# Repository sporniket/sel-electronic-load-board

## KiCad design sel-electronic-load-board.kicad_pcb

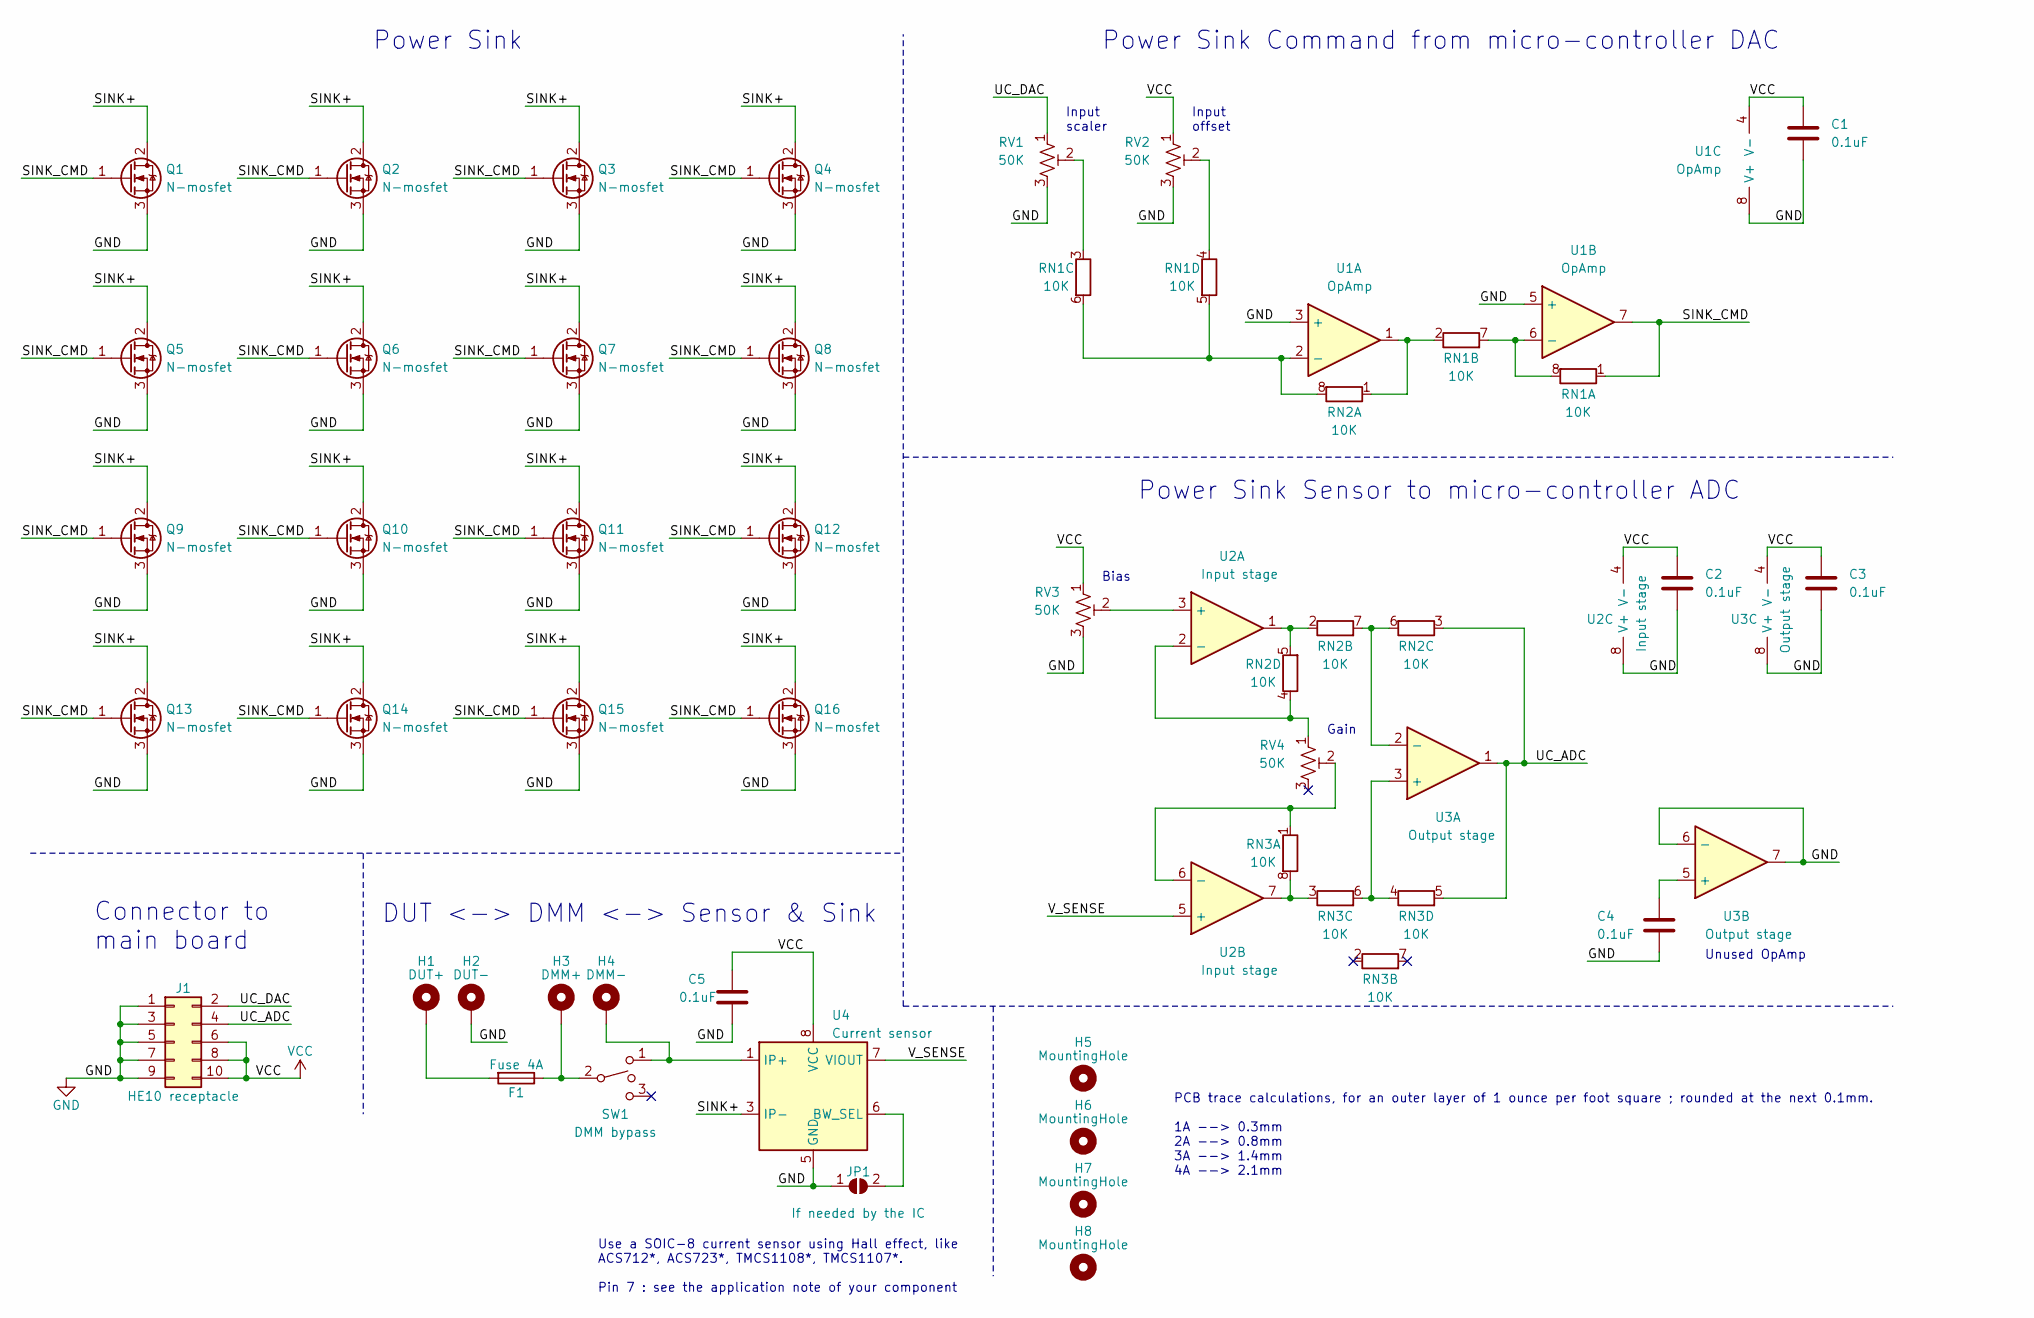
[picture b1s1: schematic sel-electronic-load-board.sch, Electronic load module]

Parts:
C1, C2, C3, C4, C5: 0.1uF; C_1206_3216Metric_Pad1.33x1.80mm_HandSolder
F1: Fuse 4A; Fuseholder_Cylinder-5x20mm_Stelvio-Kontek_PTF78_Horizontal_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
H1: DUT+; MountingHole_4.3mm_M4_Pad
H2: DUT-; MountingHole_4.3mm_M4_Pad
H3: DMM+; MountingHole_4.3mm_M4_Pad
H4: DMM-; MountingHole_4.3mm_M4_Pad
H5, H6, H7, H8: MountingHole; MountingHole_4.3mm_M4
J1: HE10 receptacle; IDC-Header_2x05_P2.54mm_Horizontal
JP1: If needed by the IC; SolderJumper-2_P1.3mm_Open_RoundedPad1.0x1.5mm
Q1, Q2, Q3, Q4, Q5, Q6, Q7, Q8, Q9, Q10, Q11, Q12, Q13, Q14, Q15, Q16: N-mosfet; TO-220-3_Vertical
RN1, RN2, RN3: 10K; R_Array_Convex_4x0603
RV1, RV2, RV3, RV4: 50K; Potentiometer_Bourns_3296Y_Vertical
SW1: DMM bypass; toggle-switch-P4.70mm-3pins-75mils-vias
U1: OpAmp; TSSOP-8_3x3mm_P0.65mm
U2: Input stage; TSSOP-8_3x3mm_P0.65mm
U3: Output stage; TSSOP-8_3x3mm_P0.65mm
U4: Current sensor; SOIC-8_3.9x4.9mm_P1.27mm

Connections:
/SINK+: Q1.2 (D), Q2.2 (D), Q3.2 (D), Q4.2 (D), Q5.2 (D), Q6.2 (D), Q7.2 (D), Q8.2 (D), Q9.2 (D), Q10.2 (D), Q11.2 (D), Q12.2 (D), Q13.2 (D), Q14.2 (D), Q15.2 (D), Q16.2 (D), U4.3 (IP-), U4.4 (IP-)
/SINK_CMD: Q1.1 (G), Q2.1 (G), Q3.1 (G), Q4.1 (G), Q5.1 (G), Q6.1 (G), Q7.1 (G), Q8.1 (G), Q9.1 (G), Q10.1 (G), Q11.1 (G), Q12.1 (G), Q13.1 (G), Q14.1 (G), Q15.1 (G), Q16.1 (G), RN1.1 (R1.1), U1.7
/UC_ADC: J1.4, RN2.3 (R3.1), RN3.5 (R4.2), U3.1
/UC_DAC: J1.2, RV1.1
/V_SENSE: U2.5 (+), U4.7 (VIOUT)
GND: C1.2, C2.2, C3.2, C4.2, C5.2, H2.1, J1.1, J1.3, J1.5, J1.7, J1.9, JP1.1 (A), Q1.3 (S), Q2.3 (S), Q3.3 (S), Q4.3 (S), Q5.3 (S), Q6.3 (S), Q7.3 (S), Q8.3 (S), Q9.3 (S), Q10.3 (S), Q11.3 (S), Q12.3 (S), Q13.3 (S), Q14.3 (S), Q15.3 (S), Q16.3 (S), RV1.3, RV2.3, RV3.3, U1.3 (+), U1.5 (+), U1.8 (V+), U2.8 (V+), U3.6 (-), U3.7, U3.8 (V+), U4.5 (GND)
unnamed: C4.1, U3.5 (+)
unnamed: F1.1, H3.1, SW1.2
unnamed: F1.2, H1.1
unnamed: H4.1, SW1.1, U4.1 (IP+), U4.2 (IP+)
unnamed: JP1.2 (B), U4.6 (BW_SEL)
unnamed: RN1.2 (R2.1), RN2.1 (R1.1), U1.1
unnamed: RN1.3 (R3.1), RV1.2
unnamed: RN1.4 (R4.1), RV2.2
unnamed: RN1.5 (R4.2), RN1.6 (R3.2), RN2.8 (R1.2), U1.2 (-)
unnamed: RN1.7 (R2.2), RN1.8 (R1.2), U1.6 (-)
unnamed: RN2.2 (R2.1), RN2.5 (R4.2), U2.1
unnamed: RN2.4 (R4.1), RV4.1, U2.2 (-)
unnamed: RN2.6 (R3.2), RN2.7 (R2.2), U3.2 (-)
unnamed: RN3.1 (R1.1), RV4.2, U2.6 (-)
unnamed: RN3.3 (R3.1), RN3.8 (R1.2), U2.7
unnamed: RN3.4 (R4.1), RN3.6 (R3.2), U3.3 (+)
unnamed: RV3.2, U2.3 (+)
VCC: C1.1, C2.1, C3.1, C5.1, J1.6, J1.8, J1.10, RV2.1, RV3.1, U1.4 (V-), U2.4 (V-), U3.4 (V-), U4.8 (VCC)

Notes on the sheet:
Power Sink
Input scaler
Input offset
Power Sink Command from micro-controller DAC
Gain
Bias
Unused OpAmp
Power Sink Sensor to micro-controller ADC
Use a SOIC-8 current sensor using Hall effect, like ACS712*, ACS723*, TMCS1108*, TMCS1107*. Pin 7 : see the application note of your component
DUT <-> DMM <-> Sensor & Sink
Connector to main board
PCB trace calculations, for an outer layer of 1 ounce per foot square ; rounded at the next 0.1mm. 1A --> 0.3mm 2A --> 0.8mm 3A --> 1.4mm 4A --> 2.1mm

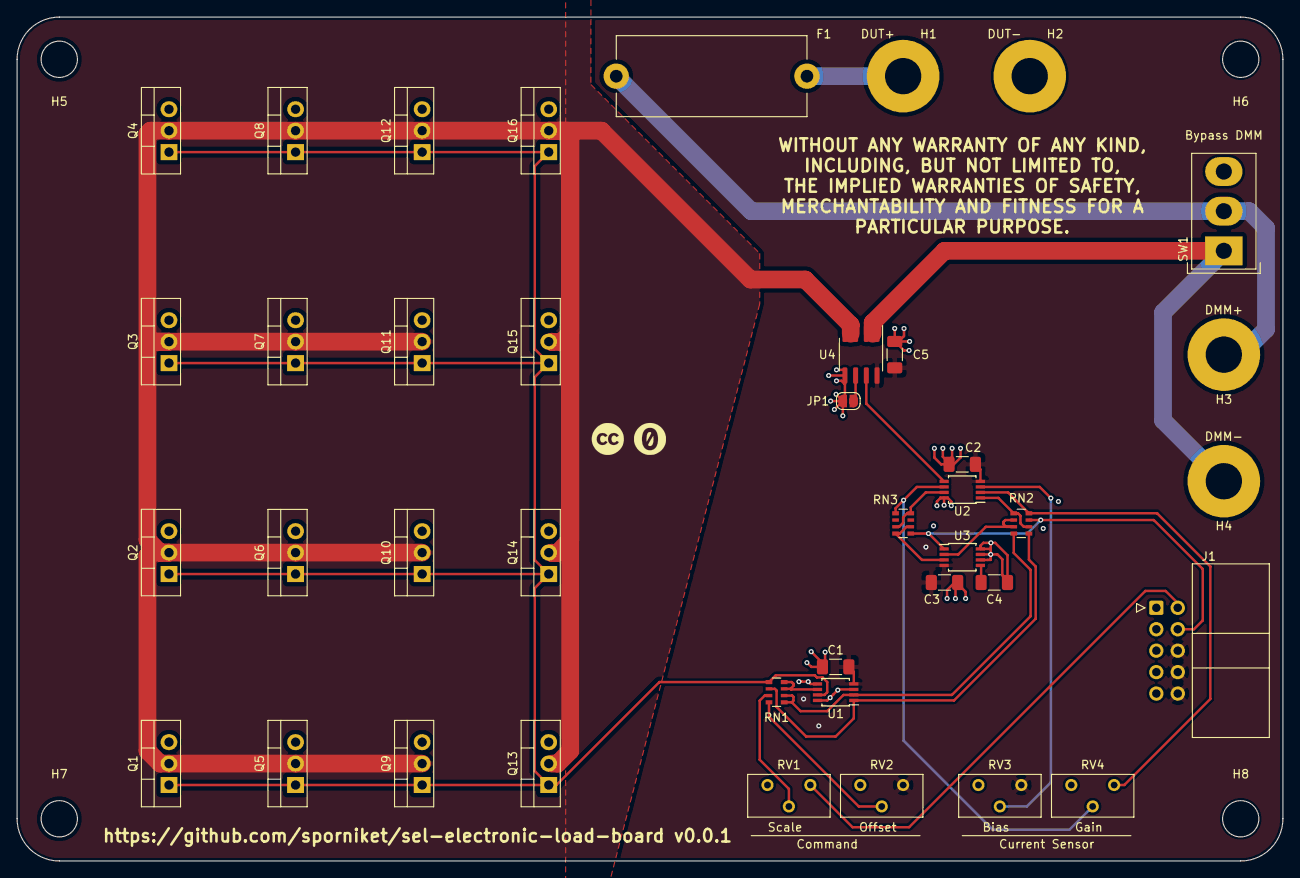
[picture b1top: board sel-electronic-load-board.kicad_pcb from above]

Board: 4 copper layers, 150.0 x 100.0 mm, 44 parts (0 on the bottom side), 24 nets.

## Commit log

2022-05-14 Schematic done
2022-05-14 Schematic almost done, need to provision pin6 of current sensor to GND
2022-05-14 implement a bypass of the external DMM
2022-05-14 reference datasheets
2022-05-14 Finished the current sensor IC
2022-05-14 annotations
2022-05-15 assigning footprint, missing lever switch
2022-05-15 handmade footprint for a toggle switch
2022-05-15 update metadata, use custom footprint for toggle switch
2022-05-15 setup pcb
2022-05-15 start laying out components : connectors and DMM bypass toggle
2022-05-19 reorganize copper pour, traces, DMM and bypass, connector to main board
2022-05-19 done tracing, optimizing the use of network resistors units
2022-05-19 prepare first release
2022-05-19 adjust labels on silkscreen
2022-05-19 adjust labels on schematics, update top overview
2022-05-19 change png for jpg in the gallery
2022-05-19 wiring of a volt-ampere display
2022-05-19 generate gerbers
